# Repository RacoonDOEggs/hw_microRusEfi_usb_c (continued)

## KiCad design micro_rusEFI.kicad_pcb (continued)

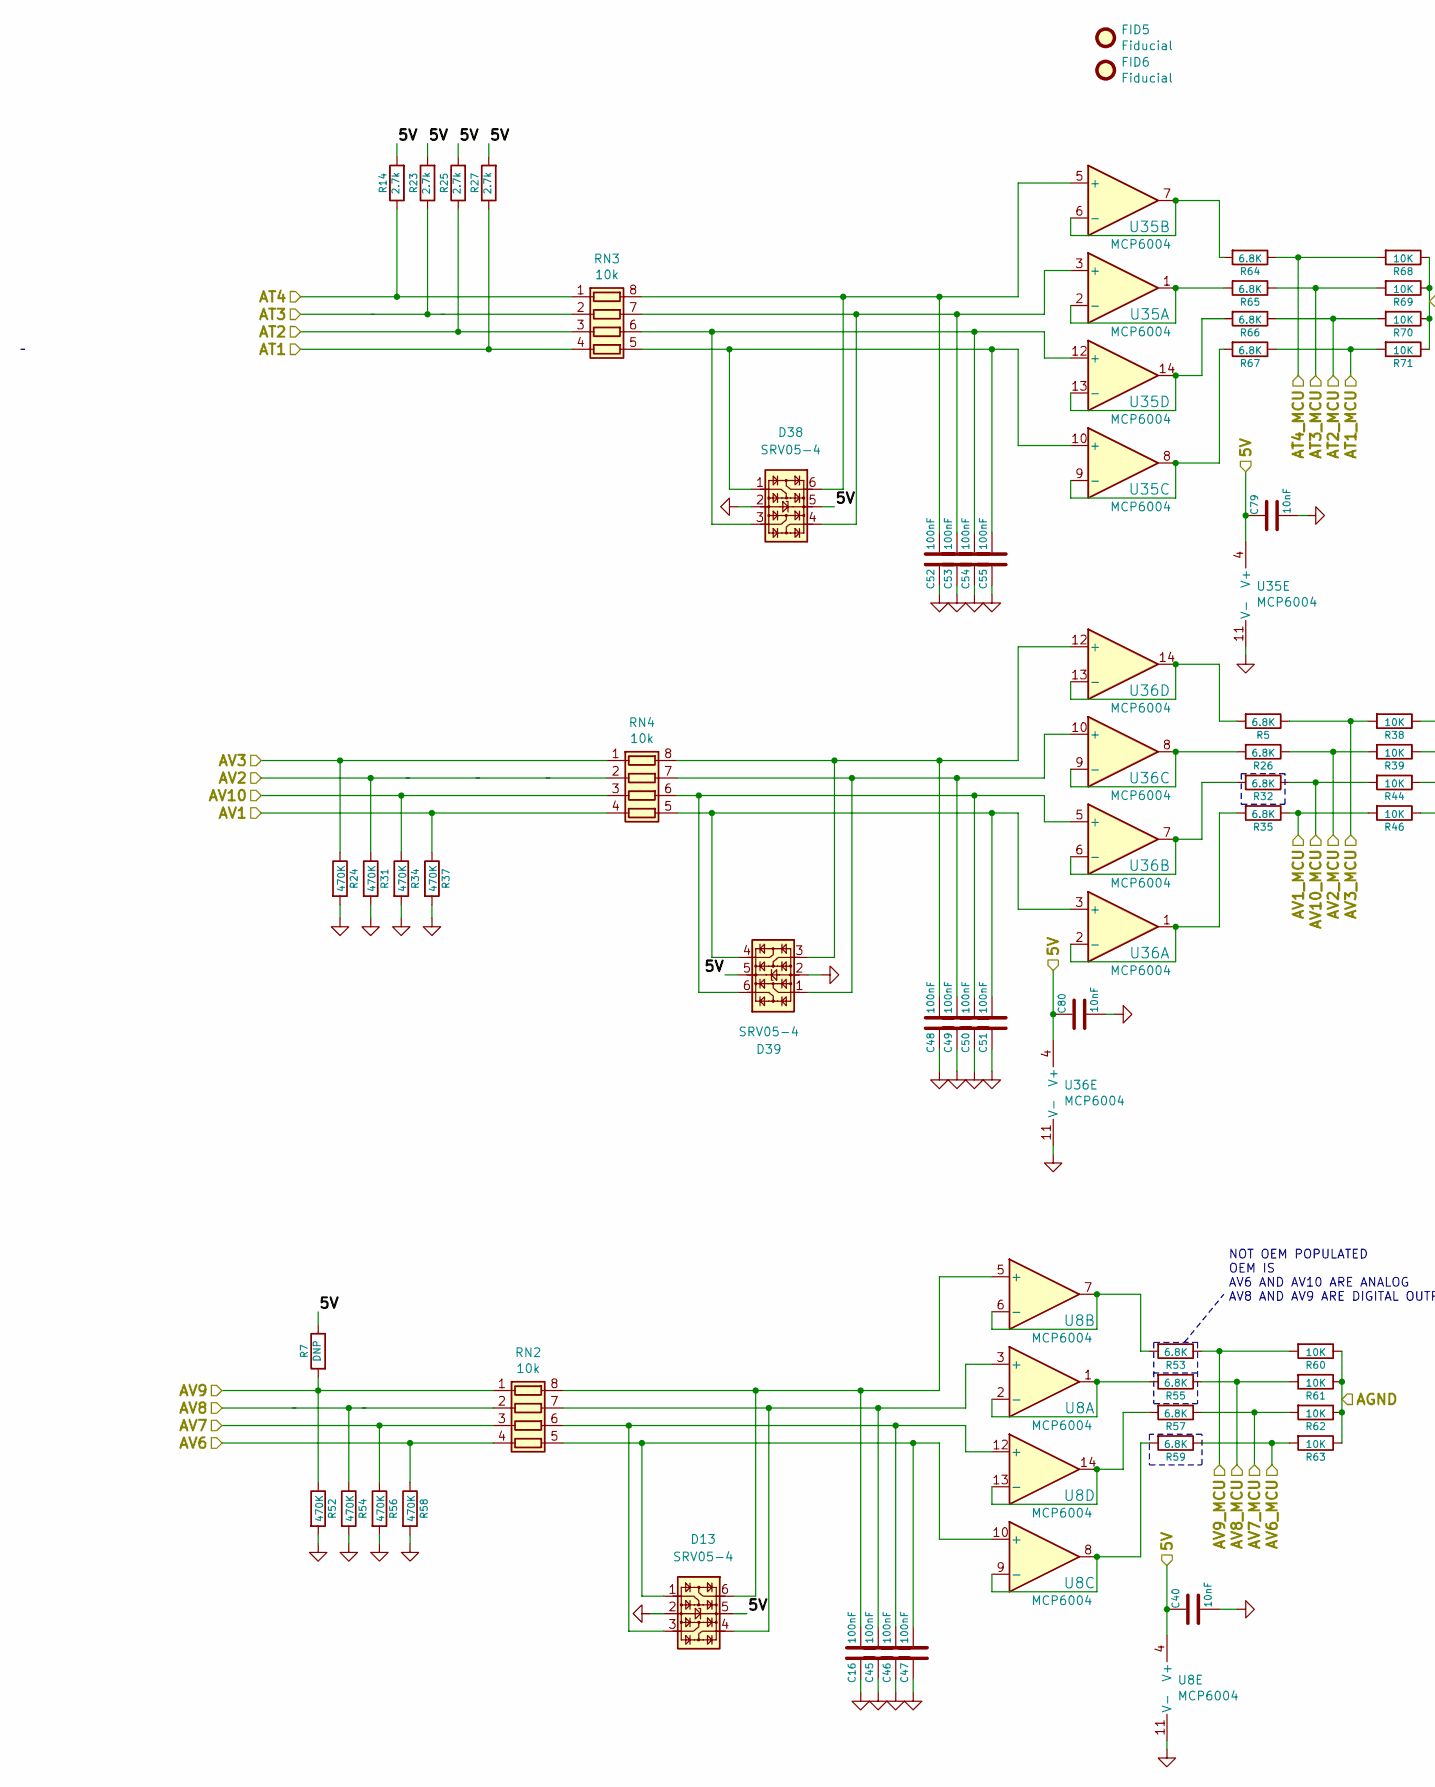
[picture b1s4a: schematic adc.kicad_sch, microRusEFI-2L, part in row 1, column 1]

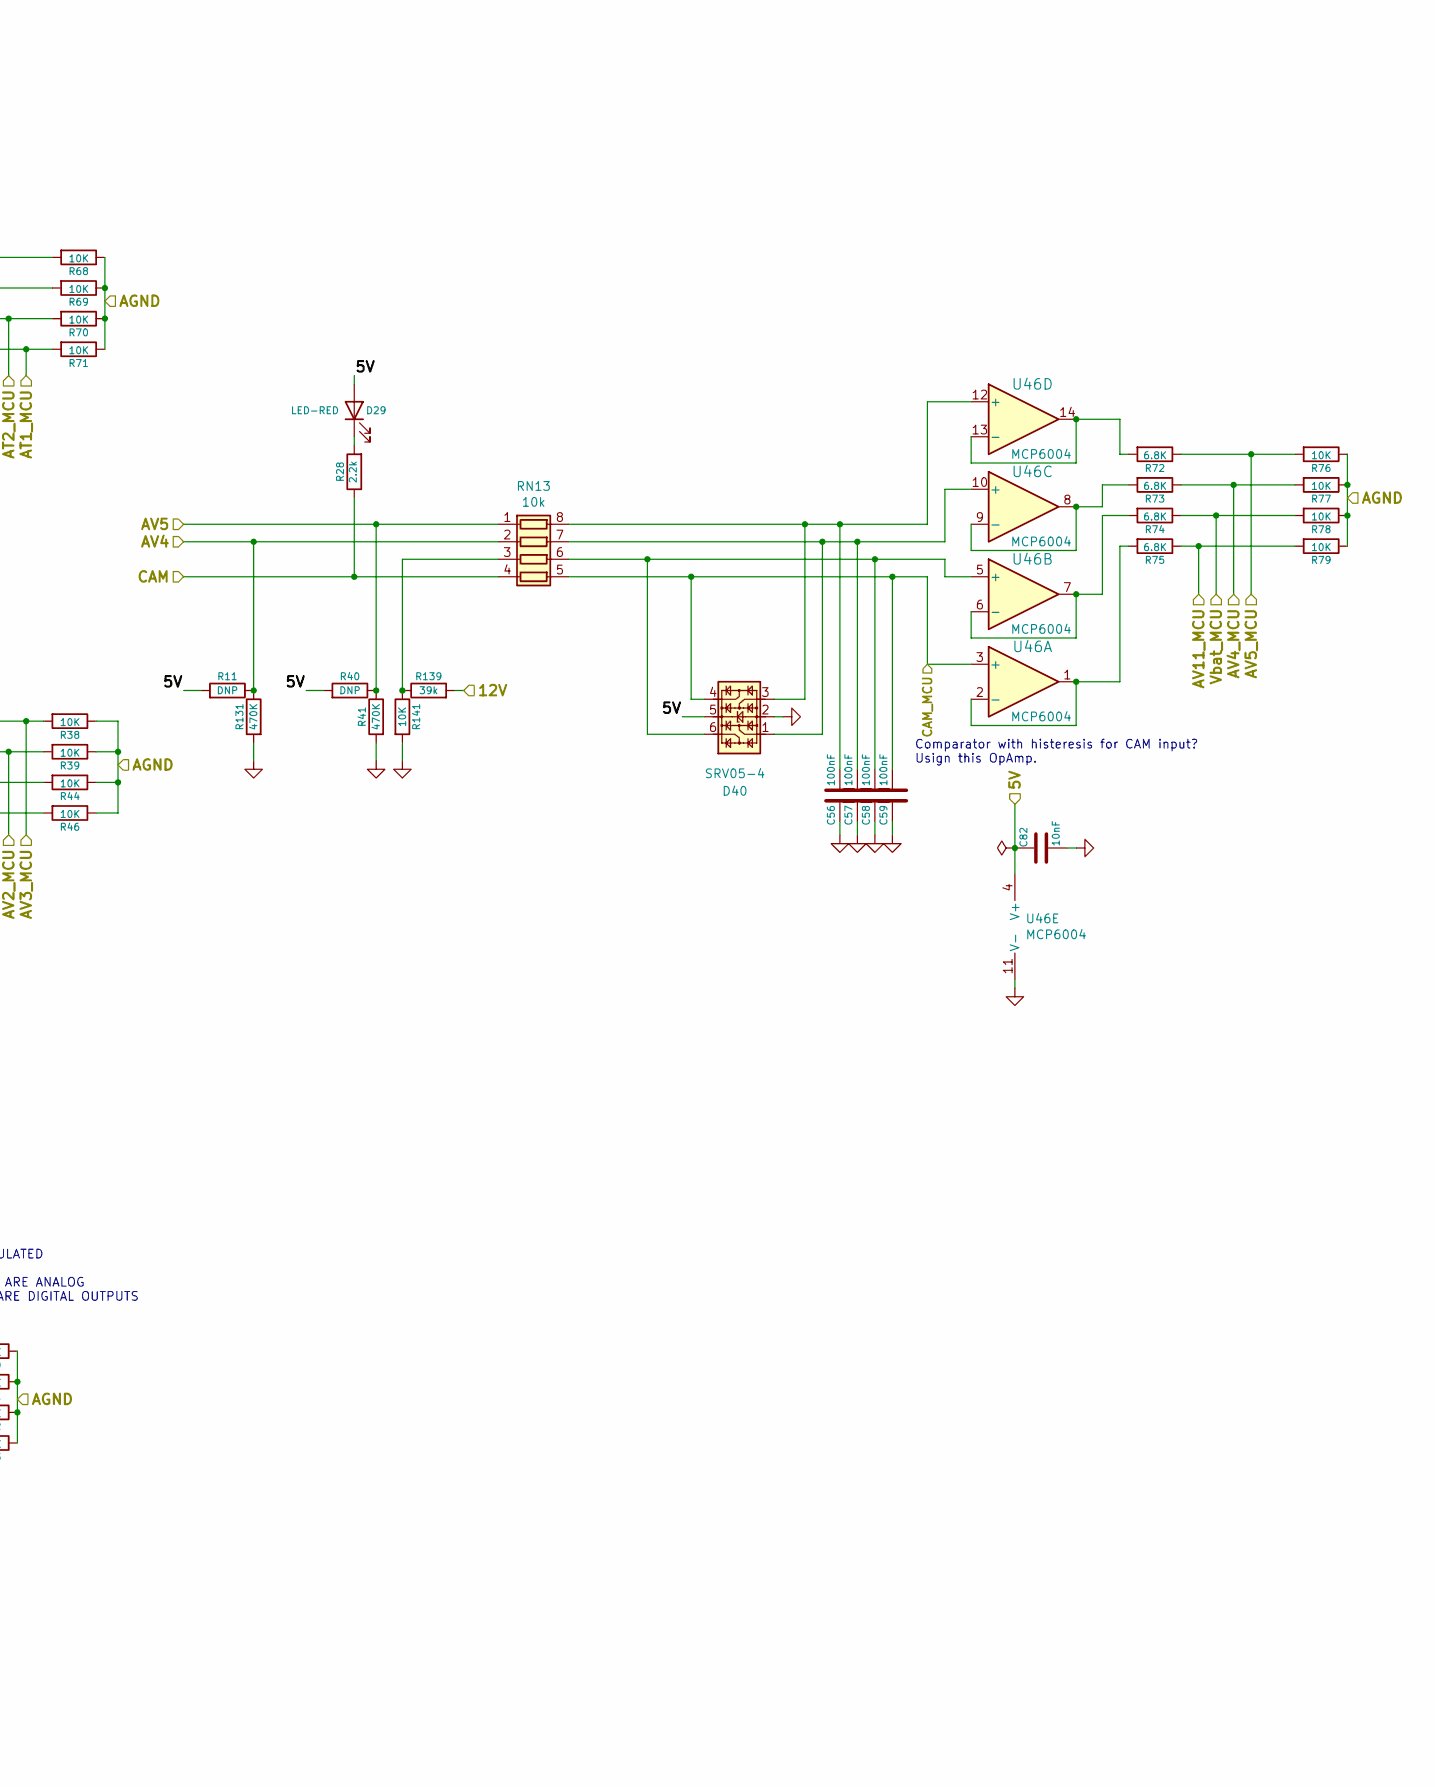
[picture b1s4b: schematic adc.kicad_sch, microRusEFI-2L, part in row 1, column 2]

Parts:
C16, C45, C46, C47, C48, C49, C50, C51, C52, C53, C54, C55, C56, C57, C58, C59: 100nF; C_0402_1005Metric; LCSC C1525
C40, C79, C80, C82: 10nF; C_0603_1608Metric; Part # C0603C103K1RACTU; LCSC C57112
D13, D38, D39, D40: SRV05-4; SOT-23-6; LCSC C85364
D29: LED-RED; LED_0603_1608Metric; LCSC C2286
FID5, FID6: Fiducial; Fiducial_0.5mm_Mask1mm; Part # DNP
R5, R26, R32, R35, R57, R59, R64, R65, R66, R67, R72, R73, R74, R75: 6.8K; R_0603_1608Metric; LCSC C23212
R7, R11, R40: DNP; R_0402_1005Metric; Part # DNP
R14, R23, R25, R27: 2.7k; R_0603_1608Metric; Part # RMCF0603FT2K70; LCSC C13167
R24, R31, R34, R37, R41, R52, R54, R56, R58, R131: 470K; R_0402_1005Metric; LCSC C25790
R28: 2.2k; R_0603_1608Metric; Part # RMCF0603FT2K20; LCSC C4190
R38, R39, R44, R46, R60, R61, R62, R63, R68, R69, R70, R71, R76, R77, R78, R79, R141: 10K; R_0603_1608Metric; Part # RMCF0603JT10K0; LCSC C25804
R53, R55: 6.8K; R_0603_1608Metric
R139: 39k; R_0603_1608Metric; Part # RC0603FR-0739KL; LCSC C23153
RN2, RN3, RN4, RN13: 10k; R_Array_Convex_4x0603; Part # YC164-JR-0710KL; LCSC C29718
U8, U35, U36, U46: MCP6004; TSSOP-14_4.4x5mm_P0.65mm; Part # MCP6004T-I/ST; LCSC C248577

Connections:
/5V: C40.1, C79.1, C80.1, C82.1, D13.5, D29.2 (A), D38.5, D39.5, D40.5, R7.1, R11.2, R14.2, R23.2, R25.2, R27.2, R40.2, U8.4 (V+), U35.4 (V+), U36.4 (V+), U46.4 (V+); also elsewhere on the board
/12V_MREL: R139.2; also elsewhere on the board
/ADC/AGND: R38.1, R39.1, R44.1, R46.1, R60.1, R61.1, R62.1, R63.1, R68.1, R69.1, R70.1, R71.1, R76.1, R77.1, R78.1, R79.1; also elsewhere on the board
/ADC/AV11_MCU: R75.1, R79.2; also elsewhere on the board
/AT1: R27.1, RN3.4 (R4.1); also elsewhere on the board
/AT1_MCU: R67.1, R71.2; also elsewhere on the board
/AT2: R25.1, RN3.3 (R3.1); also elsewhere on the board
/AT2_MCU: R66.1, R70.2; also elsewhere on the board
/AT3: R23.1, RN3.2 (R2.1); also elsewhere on the board
/AT3_MCU: R65.1, R69.2; also elsewhere on the board
/AT4: R14.1, RN3.1 (R1.1); also elsewhere on the board
/AT4_MCU: R64.1, R68.2; also elsewhere on the board
/AV1: R37.1, RN4.4 (R4.1); also elsewhere on the board
/AV1_MCU: R35.1, R46.2; also elsewhere on the board
/AV2: R31.1, RN4.2 (R2.1); also elsewhere on the board
/AV2_MCU: R26.1, R39.2; also elsewhere on the board
/AV3: R24.1, RN4.1 (R1.1); also elsewhere on the board
/AV3_MCU: R5.1, R38.2; also elsewhere on the board
/AV4: R11.1, R131.1, RN13.2 (R2.1); also elsewhere on the board
/AV4_MCU: R73.1, R77.2; also elsewhere on the board
/AV5: R40.1, R41.1, RN13.1 (R1.1); also elsewhere on the board
/AV5_MCU: R72.1, R76.2; also elsewhere on the board
/AV6: R58.1, RN2.4 (R4.1); also elsewhere on the board
/AV6_MCU: R59.1, R63.2; also elsewhere on the board
/AV7: R56.1, RN2.3 (R3.1); also elsewhere on the board
/AV7_MCU: R57.1, R62.2; also elsewhere on the board
/AV8: R54.1, RN2.2 (R2.1); also elsewhere on the board
/AV8_MCU: R55.1, R61.2; also elsewhere on the board
/AV9: R7.2, R52.1, RN2.1 (R1.1); also elsewhere on the board
/AV9_MCU: R53.1, R60.2; also elsewhere on the board
/AV10: R34.1, RN4.3 (R3.1); also elsewhere on the board
/AV10_MCU: R32.1, R44.2; also elsewhere on the board
/CAM_MCU: C59.1, D40.4, RN13.5 (R4.2), U46.3 (+); also elsewhere on the board
/CAM_SENSOR: R28.1, RN13.4 (R4.1); also elsewhere on the board
/Vbat_MCU: R74.1, R78.2; also elsewhere on the board
GND: C16.2, C40.2, C45.2, C46.2, C47.2, C48.2, C49.2, C50.2, C51.2, C52.2, C53.2, C54.2, C55.2, C56.2, C57.2, C58.2, C59.2, C79.2, C80.2, C82.2, D13.2, D38.2, D39.2, D40.2, R24.2, R31.2, R34.2, R37.2, R41.2, R52.2, R54.2, R56.2, R58.2, R131.2, R141.2, U8.11 (V-), U35.11 (V-), U36.11 (V-), U46.11 (V-); also elsewhere on the board
unnamed: D29.1 (K), R28.2
unnamed: C16.1, D13.6, RN2.8 (R1.2), U8.5 (+)
unnamed: C45.1, D13.4, RN2.7 (R2.2), U8.3 (+)
unnamed: C46.1, D13.3, RN2.6 (R3.2), U8.12 (+)
unnamed: C47.1, D13.1, RN2.5 (R4.2), U8.10 (+)
unnamed: C52.1, D38.6, RN3.8 (R1.2), U35.5 (+)
unnamed: C53.1, D38.4, RN3.7 (R2.2), U35.3 (+)
unnamed: C54.1, D38.3, RN3.6 (R3.2), U35.12 (+)
unnamed: C55.1, D38.1, RN3.5 (R4.2), U35.10 (+)
unnamed: C48.1, D39.3, RN4.8 (R1.2), U36.12 (+)
unnamed: C49.1, D39.1, RN4.7 (R2.2), U36.10 (+)
unnamed: C50.1, D39.6, RN4.6 (R3.2), U36.5 (+)
unnamed: C51.1, D39.4, RN4.5 (R4.2), U36.3 (+)
unnamed: C56.1, D40.3, RN13.8 (R1.2), U46.12 (+)
unnamed: C57.1, D40.1, RN13.7 (R2.2), U46.10 (+)
unnamed: R139.1, R141.1, RN13.3 (R3.1)
unnamed: C58.1, D40.6, RN13.6 (R3.2), U46.5 (+)
unnamed: R55.2, U8.1, U8.2 (-)
unnamed: R53.2, U8.6 (-), U8.7
unnamed: R59.2, U8.8, U8.9 (-)
unnamed: R57.2, U8.13 (-), U8.14
unnamed: R65.2, U35.1, U35.2 (-)
unnamed: R64.2, U35.6 (-), U35.7
unnamed: R67.2, U35.8, U35.9 (-)
unnamed: R66.2, U35.13 (-), U35.14
unnamed: R35.2, U36.1, U36.2 (-)
unnamed: R32.2, U36.6 (-), U36.7
unnamed: R26.2, U36.8, U36.9 (-)
unnamed: R5.2, U36.13 (-), U36.14
unnamed: R75.2, U46.1, U46.2 (-)
unnamed: R74.2, U46.6 (-), U46.7
unnamed: R73.2, U46.8, U46.9 (-)
unnamed: R72.2, U46.13 (-), U46.14

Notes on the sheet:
Comparator with histeresis for CAM input? Usign this OpAmp.
NOT OEM POPULATED OEM IS AV6 AND AV10 ARE ANALOG AV8 AND AV9 ARE DIGITAL OUTPUTS

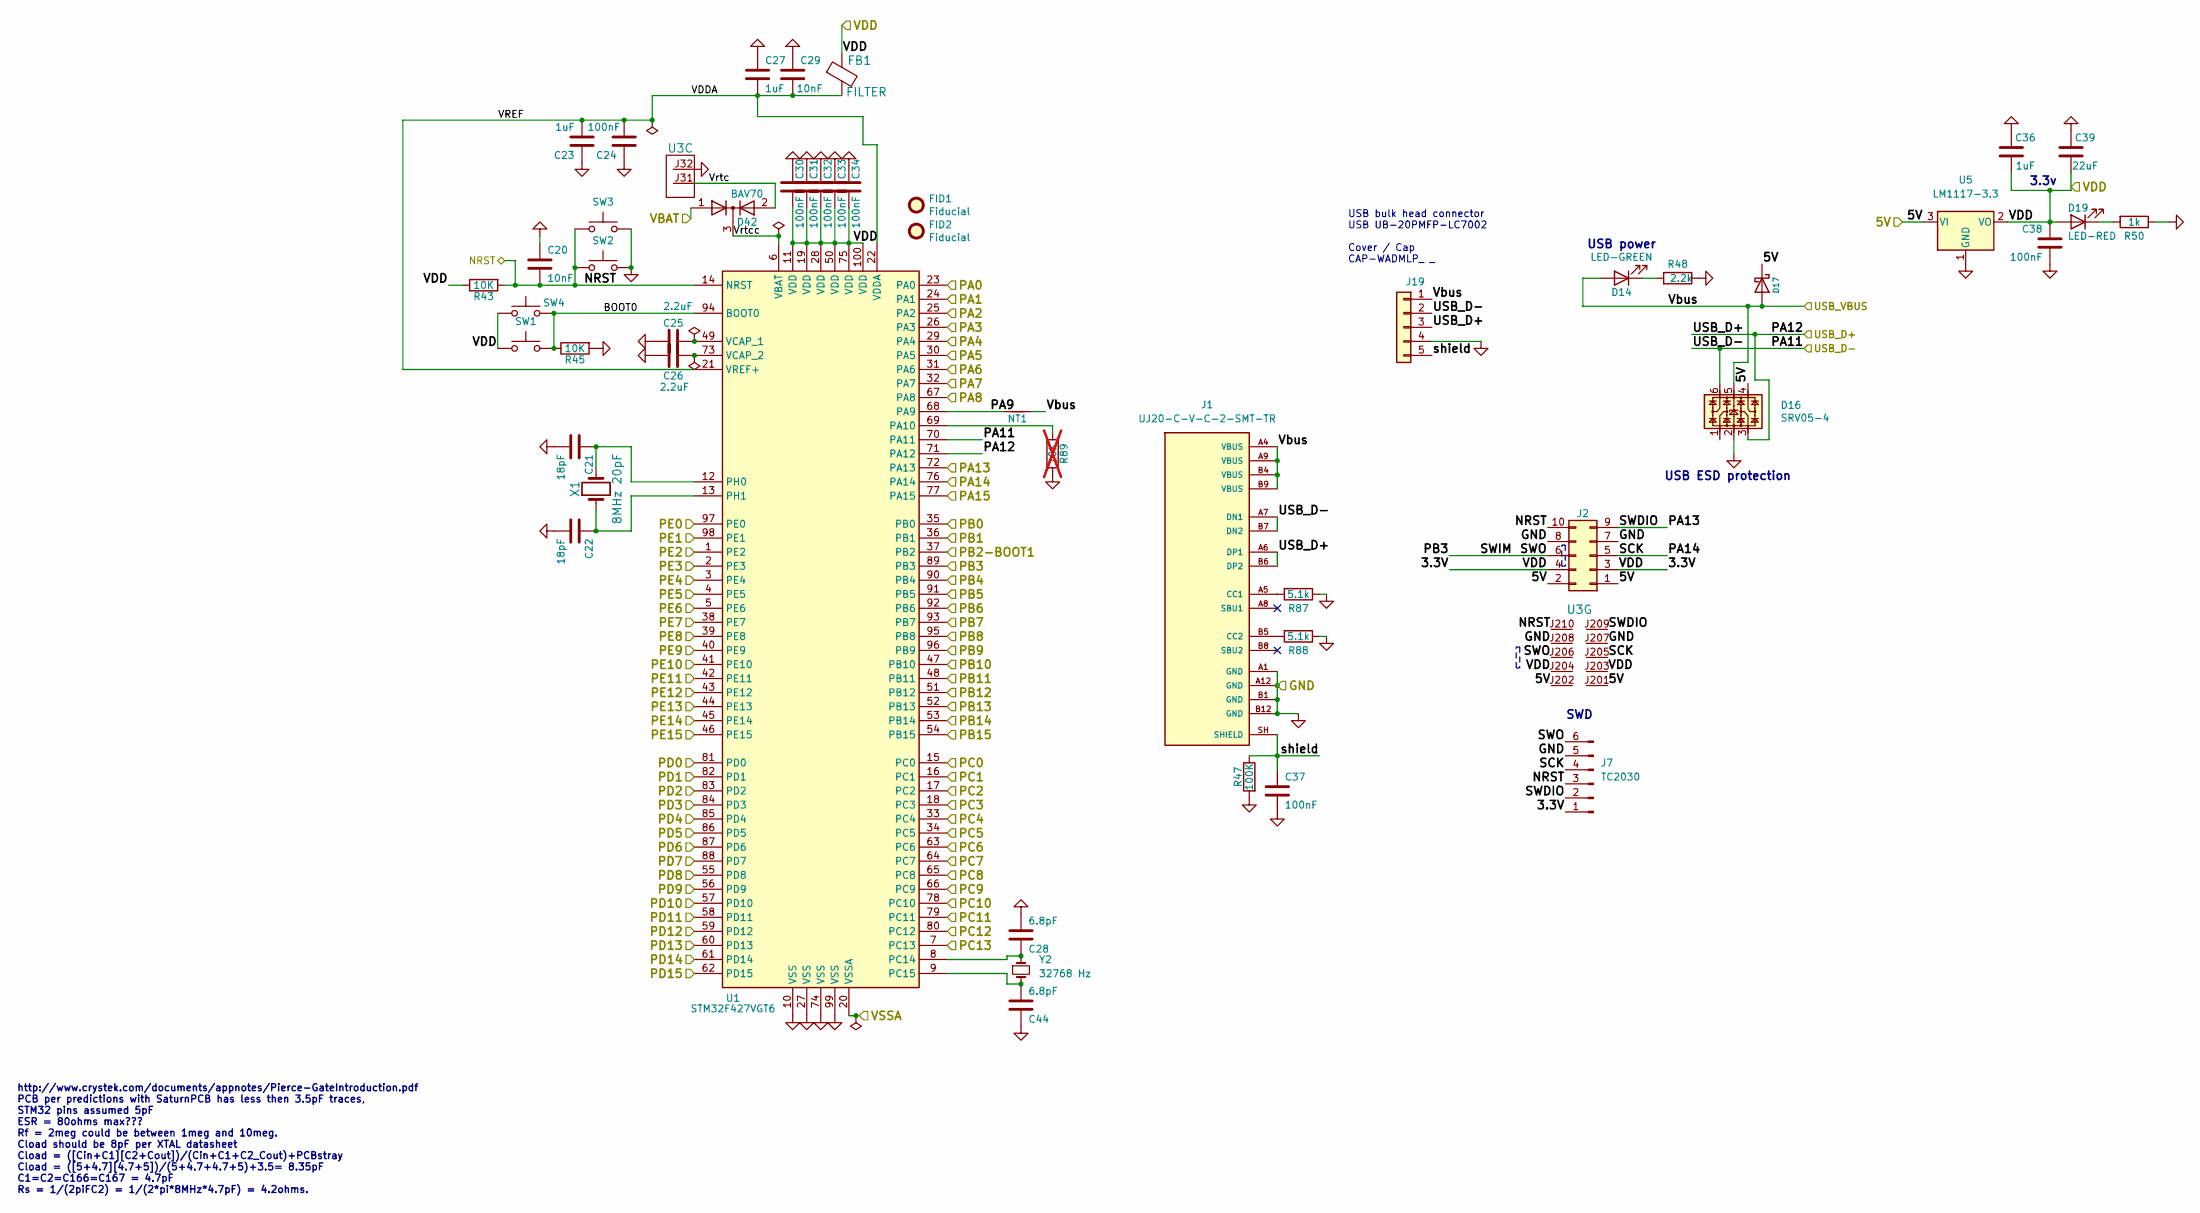
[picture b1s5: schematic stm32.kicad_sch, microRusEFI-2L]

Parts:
C20, C29: 10nF; C_0603_1608Metric; Part # C0603C103K1RACTU; LCSC C57112
C21, C22: 18pF; C_0603_1608Metric; Part # CL10C180JB8NNNC; LCSC C1647
C23, C27, C36: 1uF; C_0603_1608Metric; Part # UMK107BJ105KA-T; LCSC C15849
C24, C30, C31, C32, C33, C34, C37, C38: 100nF; C_0603_1608Metric; Part # C0603C104J5RACTU; LCSC C14663
C25, C26: 2.2uF; C_0603_1608Metric; Part # GRM188R6YA225KA12D; LCSC C23630
C28, C44: 6.8pF; C_0603_1608Metric; LCSC C1679
C39: 22uF; C_0805_2012Metric; LCSC C59461
D14: LED-GREEN; LED_0805_2012Metric; LCSC C2297
D16: SRV05-4; SOT-23-6; LCSC C85364
D17: B5819W; D_SOD-123; LCSC C8598
D19: LED-RED; LED_0603_1608Metric; LCSC C2286
D42: BAV70; SOT-23; LCSC C82479
FB1: FILTER; R_0603_1608Metric_Pad1.05x0.95mm_HandSolder; Part # BLM21PG221SN1D; LCSC C1034
FID1, FID2: Fiducial; Fiducial_0.5mm_Mask1mm; Part # DNP
J1: UJ20-C-V-C-2-SMT-TR; CUI_UJ20-C-V-C-2-SMT-TR; PARTREV 1.0
J2: Conn_02x05_Odd_Even; PinSocket_2x05_P2.54mm_Vertical_SMD; Part # 95278-801B10LF
J7: TC2030; Tag-Connect_TC2030-IDC-NL_2x03_P1.27mm_Vertical
J19: Conn_01x06; JST_EH_B5B-EH-A_1x05_P2.50mm_Vertical
NT1: Net-Tie_2; Net-Tie_2_8.5mil
R43, R45: 10K; R_0603_1608Metric; Part # RMCF0603JT10K0; LCSC C25804
R47: 100K; R_0603_1608Metric; Part # RMCF0603JT100K; LCSC C25803
R48: 2.2k; R_0603_1608Metric; Part # RMCF0603FT2K20; LCSC C4190
R50: 1k; R_0603_1608Metric; Part # RMCF0603JJ1K00; LCSC C21190
R87, R88: 5.1k; R_0603_1608Metric; Part # RMCF0603JJ1K00; LCSC C21190
R89: 10K; R_0603_1608Metric; Part # RMCF0603JT10K0; LCSC C25804; not fitted
SW1, SW2: SW_Push; SW_SPST_CK_RS282G05A3; LCSC C398054
SW3, SW4: SW_Push; SW_Push_SPST_NO_Alps_SKRK
U1: STM32F427VGT6; LQFP-100_14x14mm_P0.5mm; Part # STM32F427VGT6; LCSC C117815
U3: molex_48pin_MRE
U5: LM1117-3.3; SOT-223-3_TabPin2; LCSC C6186
X1: 8MHz 20pF; Crystal_SMD_5032-2Pin_5.0x3.2mm; LCSC C115962
Y2: 32768 Hz; Crystal_SMD_3215-2Pin_3.2x1.5mm; LCSC C32346

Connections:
/5V: D16.4, D17.1 (K), J2.1, J2.2, U3.J201, U3.J202, U5.3 (VI); also elsewhere on the board
/ADC/AGND: U1.20 (VSSA); also elsewhere on the board
/AT1_MCU: U1.23 (PA0); also elsewhere on the board
/AT2_MCU: U1.24 (PA1); also elsewhere on the board
/AT3_MCU: U1.25 (PA2); also elsewhere on the board
/AT4_MCU: U1.26 (PA3); also elsewhere on the board
/AV1_MCU: U1.15 (PC0); also elsewhere on the board
/AV2_MCU: U1.31 (PA6); also elsewhere on the board
/AV3_MCU: U1.32 (PA7); also elsewhere on the board
/AV4_MCU: U1.17 (PC2); also elsewhere on the board
/AV5_MCU: U1.18 (PC3); also elsewhere on the board
/AV6_MCU: U1.33 (PC4); also elsewhere on the board
/AV7_MCU: U1.34 (PC5); also elsewhere on the board
/AV8_MCU: U1.35 (PB0); also elsewhere on the board
/AV9_MCU: U1.36 (PB1); also elsewhere on the board
/AV10_MCU: U1.29 (PA4); also elsewhere on the board
/CAM_MCU: U1.30 (PA5); also elsewhere on the board
/CRANK: U1.63 (PC6); also elsewhere on the board
/CS_TLE: U1.86 (PD5); also elsewhere on the board
/FlashMemory/CS: U1.46 (PE15); also elsewhere on the board
/FlashMemory/SCK: U1.52 (PB13); also elsewhere on the board
/FlashMemory/SI: U1.54 (PB15); also elsewhere on the board
/FlashMemory/SO: U1.53 (PB14); also elsewhere on the board
/H-BRIDGE/DIR: U1.67 (PA8); also elsewhere on the board
/H-BRIDGE/DIS: U1.65 (PC8); also elsewhere on the board
/H-BRIDGE/PWM: U1.64 (PC7); also elsewhere on the board
/H-BRIDGE/SO: U1.66 (PC9); also elsewhere on the board
/MCU/BOOT0: R45.1, SW1.2, SW4.2, U1.94 (BOOT0)
/MCU/PA9: NT1.1, U1.68 (PA9)
/MCU/PA13: J2.9, J7.2, U1.72 (PA13), U3.J209
/MCU/PA14: J2.5, J7.4, U1.76 (PA14), U3.J205
/MCU/PB2-BOOT1: U1.37 (PB2); also elsewhere on the board
/MCU/PB6: U1.92 (PB6); also elsewhere on the board
/MCU/PB7: U1.93 (PB7); also elsewhere on the board
/MCU/PB12: U1.51 (PB12); also elsewhere on the board
/MCU/PD0: U1.81 (PD0); also elsewhere on the board
/MCU/PD1: U1.82 (PD1); also elsewhere on the board
/MCU/PD2: U1.83 (PD2); also elsewhere on the board
/MCU/PD3: U1.84 (PD3); also elsewhere on the board
/MCU/PD4: U1.85 (PD4); also elsewhere on the board
/MCU/PD6: U1.87 (PD6); also elsewhere on the board
/MCU/PD7: U1.88 (PD7); also elsewhere on the board
/MCU/PD8: U1.55 (PD8); also elsewhere on the board
/MCU/PD9: U1.56 (PD9); also elsewhere on the board
/MCU/PD10: U1.57 (PD10); also elsewhere on the board
/MCU/PD11: U1.58 (PD11); also elsewhere on the board
/MCU/PE5: U1.4 (PE5); also elsewhere on the board
/MCU/PE6: U1.5 (PE6); also elsewhere on the board
/MCU/PE7: U1.38 (PE7); also elsewhere on the board
/MCU/PE8: U1.39 (PE8); also elsewhere on the board
/MCU/PE9: U1.40 (PE9); also elsewhere on the board
/MCU/PE10: U1.41 (PE10); also elsewhere on the board
/MCU/PE11: U1.42 (PE11); also elsewhere on the board
/MCU/PE12: U1.43 (PE12); also elsewhere on the board
/MCU/PE13: U1.44 (PE13); also elsewhere on the board
/MCU/PE14: U1.45 (PE14); also elsewhere on the board
/MCU/VBAT: D42.1 (A); also elsewhere on the board
/MCU/VDDA: C23.2, C24.2, C27.2, C29.2, FB1.2, U1.21 (VREF+), U1.22 (VDDA)
/MCU/Vbus: D14.2 (A), D16.5, D17.2 (A), J1.A4 (VBUS), J1.A9 (VBUS), J1.B4 (VBUS), J1.B9 (VBUS), J19.1, NT1.2; also elsewhere on the board
/MCU/Vrtc: D42.2 (A), U3.J31
/MCU/Vrtcc: D42.3 (K), U1.6 (VBAT)
/MCU/shield: C37.1, J1.SH (SHIELD), J19.5, R47.1
/PA15: U1.77 (PA15); also elsewhere on the board
/PB8: U1.95 (PB8); also elsewhere on the board
/PB9: U1.96 (PB9); also elsewhere on the board
/PB10: U1.47 (PB10); also elsewhere on the board
/PB11: U1.48 (PB11); also elsewhere on the board
/PC10: U1.78 (PC10); also elsewhere on the board
/PC11: U1.79 (PC11); also elsewhere on the board
/PC12: U1.80 (PC12); also elsewhere on the board
/PC13: U1.7 (PC13); also elsewhere on the board
/PD12: U1.59 (PD12); also elsewhere on the board
/PD13: U1.60 (PD13); also elsewhere on the board
/PD14: U1.61 (PD14); also elsewhere on the board
/PD15: U1.62 (PD15); also elsewhere on the board
/PE0: U1.97 (PE0); also elsewhere on the board
/PE1: U1.98 (PE1); also elsewhere on the board
/PE2: U1.1 (PE2); also elsewhere on the board
/PE3: U1.2 (PE3); also elsewhere on the board
/PE4: U1.3 (PE4); also elsewhere on the board
/RST: C20.2, J2.10, J7.3, R43.2, SW2.1, SW3.1, U1.14 (NRST), U3.J210; also elsewhere on the board
/SCK: J2.6, J7.6, U1.89 (PB3), U3.J206; also elsewhere on the board
/SI: U1.91 (PB5); also elsewhere on the board
/SO: U1.90 (PB4); also elsewhere on the board
/USB_D+: D16.3, J1.A6 (DP1), J1.B6 (DP2), J19.3, U1.71 (PA12); also elsewhere on the board
/USB_D-: D16.6, J1.A7 (DN1), J1.B7 (DN2), J19.2, U1.70 (PA11); also elsewhere on the board
/VDD: C30.2, C31.2, C32.2, C33.2, C34.2, C36.2, C38.1, C39.2, D19.2 (A), FB1.1, J2.3, J2.4, J7.1, R43.1, SW1.1, SW4.1, U1.11 (VDD), U1.19 (VDD), U1.28 (VDD), U1.50 (VDD), U1.75 (VDD), U1.100 (VDD), U3.J203, U3.J204, U5.2 (VO); also elsewhere on the board
/Vbat_MCU: U1.16 (PC1); also elsewhere on the board
GND: C20.1, C21.2, C22.2, C23.1, C24.1, C25.2, C26.2, C27.1, C28.2, C29.1, C30.1, C31.1, C32.1, C33.1, C34.1, C36.1, C37.2, C38.2, C39.1, C44.1, D16.2, J1.A1 (GND), J1.A12 (GND), J1.B1 (GND), J1.B12 (GND), J2.7, J2.8, J7.5, J19.4, R45.2, R47.2, R48.1, R50.1, R87.1, R88.1, R89.1, SW2.2, SW3.2, U1.10 (VSS), U1.27 (VSS), U1.74 (VSS), U1.99 (VSS), U3.J32, U3.J207, U3.J208, U5.1 (GND); also elsewhere on the board
unnamed: D14.1 (K), R48.2
unnamed: D19.1 (K), R50.2
unnamed: J1.A5 (CC1), R87.2
unnamed: J1.B5 (CC2), R88.2
unnamed: R89.2, U1.69 (PA10)
unnamed: C28.1, U1.8 (PC14), Y2.1
unnamed: C44.2, U1.9 (PC15), Y2.2
unnamed: C21.1, U1.12 (PH0), X1.2
unnamed: C22.1, U1.13 (PH1), X1.1
unnamed: C25.1, U1.49 (VCAP_1)
unnamed: C26.1, U1.73 (VCAP_2)

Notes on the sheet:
SWD
USB bulk head connector USB UB-20PMFP-LC7002 Cover / Cap CAP-WADMLP_ _
http://www.crystek.com/documents/appnotes/Pierce-GateIntroduction.pdf PCB per predictions with SaturnPCB has less then 3.5pF traces, STM32 pins assumed 5pF ESR = 80ohms max??? Rf = 2meg could be between 1meg and 10meg. Cload should be 8pF per XTAL datasheet Cload = ([Cin+C1][C2+Cout])/(Cin+C1+C2_Co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
3.3v
USB power
USB ESD protection

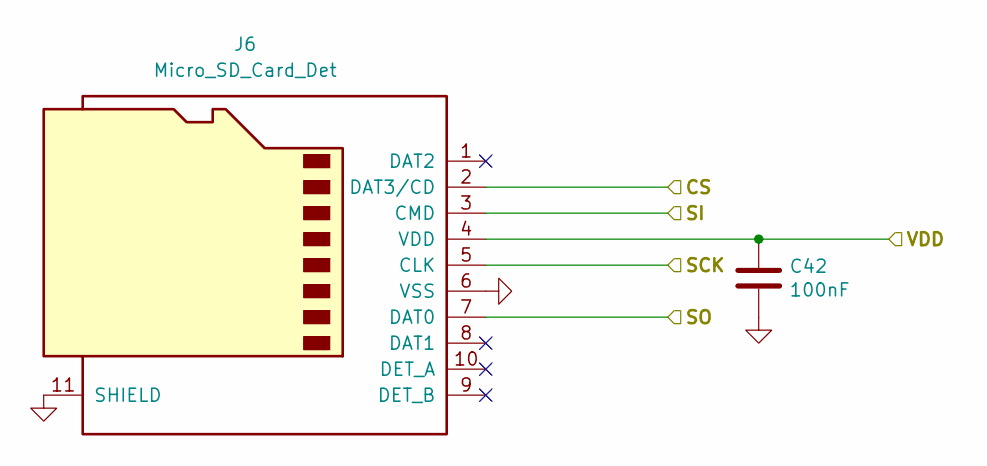
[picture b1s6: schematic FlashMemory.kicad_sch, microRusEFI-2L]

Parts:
C42: 100nF; C_0603_1608Metric; Part # C0603C104J5RACTU; LCSC C14663
J6: Micro_SD_Card_Det; microSD_HC_Molex_104031-0811; LCSC C585350

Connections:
/FlashMemory/CS: J6.2 (DAT3/CD); also elsewhere on the board
/FlashMemory/SCK: J6.5 (CLK); also elsewhere on the board
/FlashMemory/SI: J6.3 (CMD); also elsewhere on the board
/FlashMemory/SO: J6.7 (DAT0); also elsewhere on the board
/VDD: C42.1, J6.4 (VDD); also elsewhere on the board
GND: C42.2, J6.6 (VSS), J6.11 (SHIELD); also elsewhere on the board

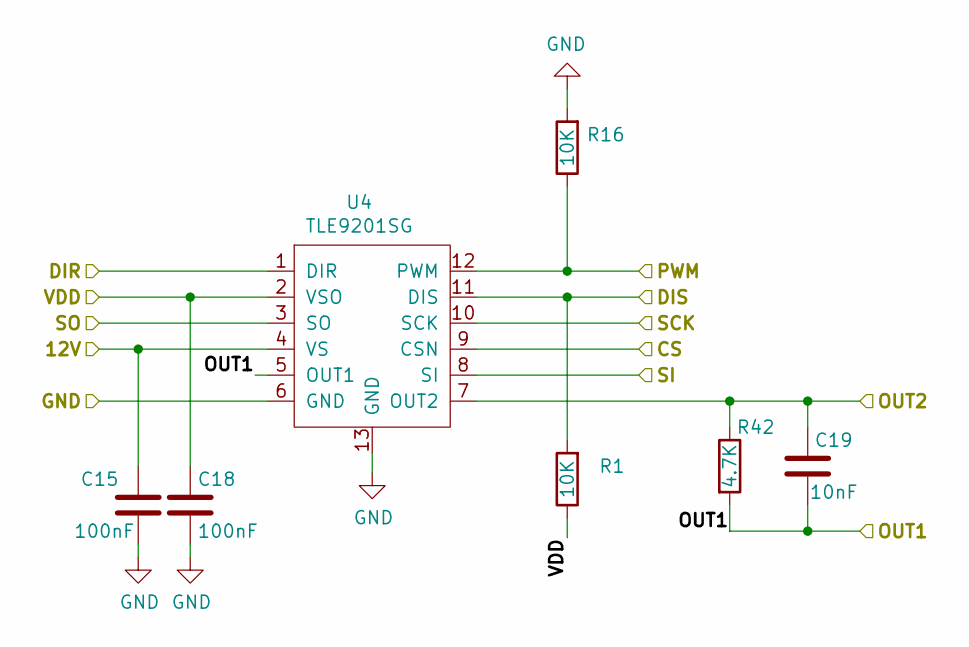
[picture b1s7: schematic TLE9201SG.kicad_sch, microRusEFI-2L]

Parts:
C15, C18: 100nF; C_0603_1608Metric; Part # C0603C104J5RACTU; LCSC C14663
C19: 10nF; C_0603_1608Metric; Part # C0603C103K1RACTU; LCSC C57112
R1, R16: 10K; R_0603_1608Metric; Part # RMCF0603JT10K0; LCSC C25804
R42: 4.7K; R_0603_1608Metric; Part # RMCF0603JT4K70; LCSC C23162
U4: TLE9201SG; Infineon_PG-DSO-12-11; Part # TLE9201SG; LCSC C112633

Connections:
/12V_MREL: C15.1, U4.4 (VS); also elsewhere on the board
/E-THROTTLE+: C19.2, R42.2, U4.5 (OUT1); also elsewhere on the board
/E-THROTTLE-: C19.1, R42.1, U4.7 (OUT2); also elsewhere on the board
/H-BRIDGE/DIR: U4.1 (DIR); also elsewhere on the board
/H-BRIDGE/DIS: R1.2, U4.11 (DIS); also elsewhere on the board
/H-BRIDGE/PWM: R16.1, U4.12 (PWM); also elsewhere on the board
/H-BRIDGE/SO: U4.3 (SO); also elsewhere on the board
/VDD: C18.1, R1.1, U4.2 (VSO); also elsewhere on the board
GND: C15.2, C18.2, R16.2, U4.6 (GND), U4.8 (SI), U4.9 (CSN), U4.10 (SCK), U4.13 (GND); also elsewhere on the board

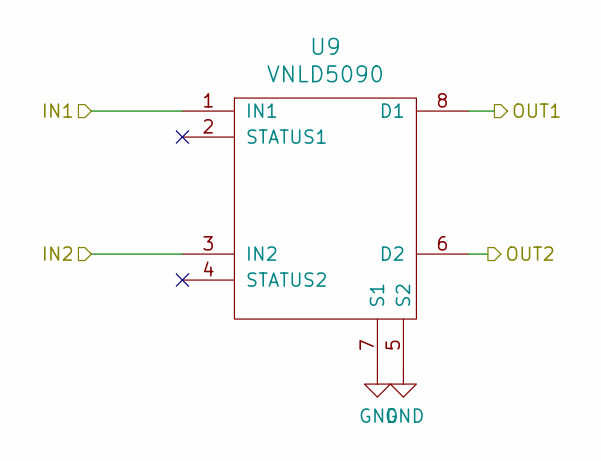
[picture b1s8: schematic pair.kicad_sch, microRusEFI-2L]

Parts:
U9: VNLD5090; SO-8_3.9x4.9mm_P1.27mm; LCSC C377942

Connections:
/AV6: U9.6 (D2); also elsewhere on the board
/AV10: U9.8 (D1); also elsewhere on the board
/TLE_OUT12_PRE: U9.3 (IN2); also elsewhere on the board
/TLE_OUT13_PRE: U9.1 (IN1); also elsewhere on the board
GND: U9.5 (S2), U9.7 (S1); also elsewhere on the board

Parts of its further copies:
U10: VNLD5090; SO-8_3.9x4.9mm_P1.27mm; LCSC C377942

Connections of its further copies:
/AV8: U10.8 (D1); also elsewhere on the board
/AV9: U10.6 (D2); also elsewhere on the board
/TLE_OUT10_PRE: U10.3 (IN2); also elsewhere on the board
/TLE_OUT11_PRE: U10.1 (IN1); also elsewhere on the board
GND: U10.5 (S2), U10.7 (S1); also elsewhere on the board
